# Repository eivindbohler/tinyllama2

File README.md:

<div id="summary" align="center">
  
</div>

<br/>

<br/>

- A fully-fledged 486/Pentium-class PC in a tiny form factor
- Integrated Sound Blaster Pro-compatible audio
- Add a Raspberry Pi Zero 2 for Roland MT&#8209;32 and General MIDI music
- Open-source hardware schematics, board layout and BIOS - build your own!
- Perfect for playing DOS games!

> **Note**  
> YouTube walkthrough + setup coming soon!

## Table of Contents
- [Summary](#summary)
- [Project Goals](#project-goals)
- [What's New In Version 2?](#whats-new-in-version-2)
- [Full system specs](#full-system-specs-revision-21)
- [Building](#building)
  * [Sourcing Parts](#sourcing-parts)
  * [Assembly](#assembly)
  * [Programming the CH559](#programming-the-ch559)
  * [Programming the BIOS](#programming-the-bios)
  * [Installing DOS](#installing-dos)
  * [Programming the CS4237B Firmware](#programming-the-cs4237b-firmware)
- [MT-32 / General MIDI](#mt-32--general-midi)
- [WiFi Connectivity](#wifi-connectivity)
- [Wiki](#wiki)
- [Help](#help)
- [Roadmap](#roadmap)
- [Contributing](#contributing)
- [License](#license)
- [Contact](#contact)
- [Acknowledgements](#acknowledgments)

<br/>

<div>

</div>

<br/>

## Project Goals
The goal of the TinyLlama project is:
- To create a fully x86-compatible DIY DOS computer with a sound card
- To keep the size as small as possible while keeping decent connectivity
- To keep the cost low

## What's New In Version 2?
Last year I released [version 1 of the TinyLlama][tinyllama1].  
While I was very happy with it and it worked great, there were a couple of things I felt were still missing + a few bugs.  

The two main new features in version 2 are:
* Built-in hardware USB HID (keyboard+mouse) to PS/2 emulation using [rasteri's HIDman firmware][hidman] running on a CH559 microcontroller  
* On-board Wemos D1 Mini ESP8266 for providing either a Hayes-compatible modem-over-WiFi or ethernet-over-WiFi (SLIP), depending on the firmware on the ESP.

Both the CH559 and the ESP8266 can be easily re-flashed/programmed in-place.  
Look at [Programming the CH559](#programming-the-ch559) and [Programming the ESP8266][wiki-wifi].

## Full system specs (revision 2.1)
### Hardware
- **86Duino System-on-module**
  * Vortex86EX CPU running at 60-500 MHz
  * 16 KB L1 cache (can be disabled)
  * 128 KB L2 cache
  * 128 MB DDR3 RAM
  * 8 MB programmable flash ROM
- **Vortex86VGA module running off a x1 PCI-e lane**
  * Maximum resolution: 1024x768, 60 Hz
  * 4 MB SRAM
  * [Alternative graphics cards][wiki-alternative-gpus]
- **Crystal CS4237B all-in-one audio chip**
- **12mm PC-speaker**
- **CR1220 battery for persistent real-time clock**
- **Power and reset buttons**
- **Connectivity**
  * USB-C for power
  * 2 x USB Type-A connectors for HID-compliant keyboard and mice
  * 2 x USB Type-A connectors for storage devices (USB 2.0)
  * MicroSD slot for storage
  * DE-9 RS232 serial port (COM1)
  * Modem or Ethernet/SLIP over WiFi (COM2)
  * Internal 2.54mm pin-header for connecting a fan (5V or 3.3V selectable)
  * 3.5mm line-out audio jack
- **mt32-pi subsystem**
  * 40-pin connector for a Raspberry Pi Zero 2
  * Pin headers for attaching a GY-PCM5102 I²S DAC module
  * Button for toggling between MT32 / General MIDI mode
  * Button for switching between audio ROMs / soundbanks
  * 4-pin I²C connector for an OLED display

### Software
- **[Custom Coreboot/SeaBIOS ROM][bios]**
- **MS-DOS / FreeDOS**

## Building
### Sourcing Parts
Full BOM (bill of materials) can be found [in the wiki][wiki-bom].
- The TinyLlama PCB rev2.1
- Modern SMD and through-hole components, as seen in the BOM
- 86Duino system-on-module (SOM-128-EX)
- Vortex86VGA Mini PCI-e module
- Crystal CS4237B 100-pin TQFP. Discontinued, but readily available
- Wemos D1 Mini ESP8266, optional
- A CR1220 battery if you want a persistent real-time clock
- One or more USB flash drives + an optional microSD card
- A USB-C power adapter (minimum 2A)

#### For MT-32/MIDI - optional
- GY-PCM5102 DAC module
- Raspberry Pi Zero 2 W with a microSD card
- An [mt32-pi compatible OLED display][mt32-pi-oled], optional but nice

### Assembly
Solder all components onto the TinyLlama rev2.1 PCB. As always, it's easier to start with the low-profile ones first, like resistors and capacitors.
If you're willing to spend slightly more, I recommended you let the PCB manufacturer pre-assemble most of the common components for you. Plus, some of the SMD components can be a bit tricky to solder.
Take a look at the [wiki][wiki-assembly] for more in-depth assembly instructions.

### Programming the CH559
1. Download the latest firmware binary from this repo, in the `hidman-binary` folder. Alternatively, get the latest source code from the [official repo][hidman] and compile it yourself.
2. Download and install `WCHISPTool_Setup.exe` from [WCH's website][wch]. Unfortunately, this tool only supports Windows. If you're on macOS or Linux, maybe try using virtualization software, or even another computer.
3. Open the `WCHISPTool_CH54x-55x` application.
4. Make sure the TinyLlama is powered off.
5. **Remove** the jumper from the "HID_POWER" pin header on the PCB (to ensure that the computer doesn't backpower the TinyLlama).
6. Connect a USB cable (type A to type A) between one of the HID USB ports on the TinyLlama and the Windows computer.
7. Press and hold the "PRG" button on the bottom side of the TinyLlama until the CH559 device pops up in the WCHISPTool.
8. Select the firmware binary file under _Download File -> Object File1_.
9. Click the "Download" button. Hopefully you'll get a success message in the log section on the right side of the program window.
10. Disconnect the USB cable.
11. **Add** the jumper to the "HID_POWER" pin header on the PCB.
12. Connect a keyboard to one of the HID USB ports. You should be good to go!

### Programming the BIOS
When purchasing the SOM-128-EX module from DMP, its ROM chip comes preinstalled with an Arduino-like bootloader which isn't what we want. Also, the  "crossbar" is configured for using the module with the 86Duino Zero/One boards - meaning its default pin layout is completely different from what we need for the TinyLlama.

Follow these steps to flash the ROM with the TinyLlama BIOS for the first time:
1. Find a USB flash drive, must be minimum 32 MB in size (shouldn't be a problem these days). Note that not all USB drives are bootable. Use a well-known bootable drive. _NB: You have to use a USB stick for this, an SD card won't work since the crossbar is configured to use different pins on the SOM for SD traffic._
2. Do a block-level transfer of the `INITBIOS.IMG` from this repo to the USB drive. Use [Balena Etcher][balena-etcher], or the command line if you know what you're doing (macOS example):
```
$ diskutil list
(Find your USB drive, eg. /dev/disk2)
$ diskutil unmountDisk /dev/disk2
$ sudo dd if=INITBIOS.IMG of=/dev/rdisk2 bs=1m
```
3. Insert the USB flash drive into the TinyLlama and turn it on. It'll hopefully boot into MS-DOS. Then, to flash the ROM:
```
C:\>anybios w initbios.rom
```
...and reboot.  

For subsequent BIOS updates, you can use the ROM's built-in virtual floppy drive available from the boot menu (press F12).  
When booted from this you'll only need a regular USB stick (formatted as FAT16/FAT32) containing the new BIOS file.

### Installing MS-DOS
_A note on selecting the DOS type:  
I've gone with MS-DOS 6.22 for maximum compatibility.  
If you prefer FreeDOS (or another DOS variant), prepare a bootable USB installer disk and use that instead of the built-in virtual floppy._
1. Pick a bootable USB drive or Micro SD card to use as the boot drive - for MS-DOS 6.22 you'll be limited to FAT16 and 2 GB per partition (though you can have several). For FreeDOS with FAT32 you can go all the way up to 2 TB.
2. Insert it, turn on the system, press F12 to bring up the boot menu, and select the virtual floppy drive.
3. Use `fdisk` from the command prompt to partition the SD/USB drive and set it to be `Active`.
4. Restart and again select to boot from the virtual floppy.  
Use `format c: /s /u` to format the drive and copy over system files. Finally use `fdisk /mbr` to make sure the Master Boot Record is correct and the drive should be bootable.
5. Copy over the `DOS` folder from A: to C:.  
You can either do this manually and create `CONFIG.SYS` and `AUTOEXEC.BAT` files to your liking, or more conveniently, just run the `SETUP.BAT` script that'll do this for you. The provided config files lets you choose from a clean boot or a QEMM-based one with XMS, EMS and 631 kB of free conventional memory.

### Programming the CS4237B Firmware
1. Copy the `CS4237B` and `UNISOUND` folders from this GitHub repo over to your SD/USB boot drive and start the system.
2. To program the firmware, run the `RESOURCE.EXE` command below and check that you get the same output:
```
C:\>cd cs4237b
C:\CS4237B>resource /f=0x120 /r=cs4237b.asm /e

Reading data from CS4237B.ASM
Length = 292    Programming EEPROM Block: 1 2    EEPROM programmed

Verifying EEPROM:
Verifying CS4237B.ASM against EEPROM . . .      Verified OKAY
```
3. Make sure the correct `BLASTER` environment variable is set and `UNISOUND.COM` command is called from `AUTOEXEC.BAT`. Note that the 8-bit DMA channel is **1** and the IRQ is **7**:
```
SET BLASTER=A220 I7 D1 P330 T4
C:\UNISOUND\UNISOUND.EXE /V60 /VW60 /VF60 /VL60 /VP60 /VC0 /VM0
```
4. Reboot the system, and you should get the following output:
```
Universal ISA PnP Sound Card Driver for DOS v0.76f. (c) JazeFox 2019-21
-----------------------------------------------------------------------
PnP card found: [CSC7537] CS4237B
BLASTER environment var found! Loading settings...
ADD:220 WSS:534 OPL:388 IRQ:7 DMA:1/1 MPU:330/I9 CTR:120 JOY:200
Initialization done.
Crystal Mixer [VOL:85 WAV:80 FM:80 LIN:0 CD:0 MIC:0]
```
5. Feel free to experiment with the different volume levels, look at the `C:\UNISOUND\UNISOUND.TXT` file for further guidance.
6. Fire up a few games to test that Adlib, SoundBlaster FM and digital sound effects are working properly.

## MT-32 / General MIDI
If you've installed [mt32-pi][mt32-pi] on a Raspberry Pi Zero 2 and connected it to the TinyLlama, it should be ready to go using IO port 330. Use the third button from the left (labeled "SYNTH_SW" on the PCB) to switch between MT-32 and General MIDI mode.  
If you want to play old games that require "MPU-401 Intelligent Mode" (Sierra games, Monkey Island 1, etc), try running [SoftMPU][softmpu]:
```
C:\SOFTMPU\>softmpu /mpu:330 /sb:220 /irq:7
```
If you want to hook up an I²C OLED display to the mt32-pi, there's a pin header on the TinyLlama labeled "I2C_OLED". The order of the pins from 1 to 4 is: GND, VCC, SCL, SDA with pin 1 being the one closest to the 3.5mm audio jack.

## WiFi Connectivity
There's a [section][wiki-wifi] in the wiki dedicated to this, take a look.

## Wiki
For an in-depth discussion of the various components, installation, configuration, etc, take a look at the [wiki][wiki].

## Help
This project is indended for people with a fair bit of hardware- and DOS knowledge. If you have questions or need help, please look at the [wiki][wiki] and [FAQ][wiki-faq] section first.

## Roadmap
Coming.  
In the mean time feel free to post [an issue][issues] if you have tips, suggestions or want to report an error.

## License
[GNU General Public License v3.0](LICENSE)

## Contact
Development thread: [Vogons][vogons-thread]  
Mastodon: [@eivindbohler@techhub.social][mastodon]  
Twitter: [@eivindbohler][twitter]  
YouTube: [@eivindbohler][youtube]

## Acknowledgements

Many thanks to
- [Sergey Kiselev][sergeys-projects] for sparking my interest in designing and building computers.
- [Rasteri][rasteri-videos] for introducing me to the CS4237B chip.
- [The Vogons forum][vogons] for inspiration, help and support.
- [86Duino / DMP][86duino] for making a great and affordable system-on-module.
- [Dale Whinham / mt32-pi][mt32-pi] for making the best synth emulator software.

[tinyllama1]: https://github.com/eivindbohler/tinyllama
[hidman]: https://github.com/rasteri/HIDman
[wiki-alternative-gpus]: https://github.com/eivindbohler/tinyllama2/wiki/alternative-gpus
[bios]: https://github.com/eivindbohler/tinyllama2-bios

[wiki]: https://github.com/eivindbohler/tinyllama2/wiki
[wiki-assembly]: https://github.com/eivindbohler/tinyllama2/wiki/assembly
[wiki-bom]: https://github.com/eivindbohler/tinyllama2/wiki/bom
[wiki-faq]: https://github.com/eivindbohler/tinyllama2/wiki/faq
[wiki-wifi]: https://github.com/eivindbohler/tinyllama2/wiki/wifi-connectivity

[balena-etcher]: https://www.balena.io/etcher
[mt32-pi-oled]: https://github.com/dwhinham/mt32-pi/wiki/LCD-and-OLED-display
[wch]: http://www.wch-ic.com/products/CH559.html

[issues]: https://github.com/eivindbohler/tinyllama2/issues

[vogons-thread]: https://www.vogons.org/viewtopic.php?t=84880
[mastodon]: https://techhub.social/@eivindbohler
[twitter]: https://twitter.com/eivindbohler
[youtube]: https://youtube.com/@eivindbohler

[sergeys-projects]: http://www.malinov.com/Home/sergeys-projects
[rasteri-videos]: https://www.youtube.com/user/TheRasteri/videos
[vogons]: https://www.vogons.org
[86duino]: https://www.86duino.com
[mt32-pi]: https://github.com/dwhinham/mt32-pi
[softmpu]: http://bjt42.github.io/softmpu

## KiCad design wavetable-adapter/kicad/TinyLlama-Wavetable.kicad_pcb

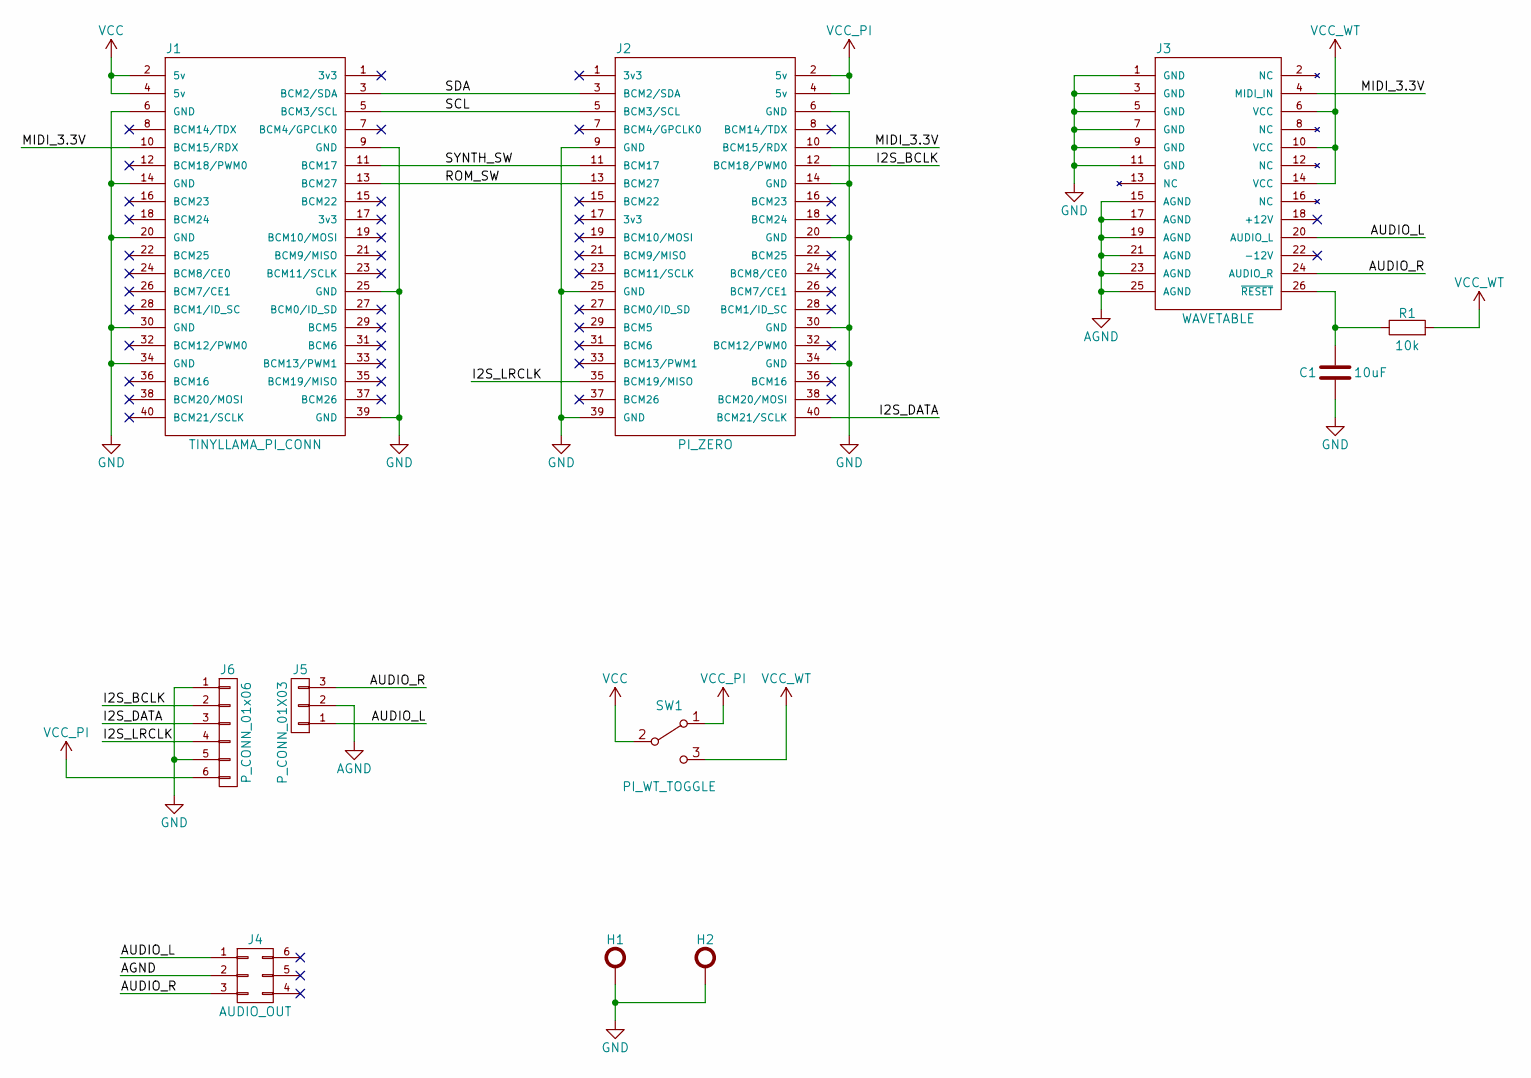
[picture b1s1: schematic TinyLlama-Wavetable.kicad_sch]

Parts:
C1: 10uF; C_0603_1608Metric
H1, H2: H_HOLE; H_440_HOLE
J1: TINYLLAMA_PI_CONN; J_CONN_RPI_MIRRORED_SMD
J2: PI_ZERO; J_CONN_RPI_SMD
J3: WAVETABLE; J_CONN_WAVETABLE
J4: AUDIO_OUT; P_CONN_02X03_SMD
J5: P_CONN_01X03; P_CONN_01X03_SMD
J6: P_CONN_01x06; P_CONN_01X06_SMD
R1: 10k; R_0603_1608Metric
SW1: PI_WT_TOGGLE; SW_1MS1T2B4M6QES

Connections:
/AUDIO_L: J3.20 (AUDIO_L), J4.1, J5.1
/AUDIO_R: J3.24 (AUDIO_R), J4.3, J5.3
/I2S_BCLK: J2.12 (BCM18/PWM0), J6.2
/I2S_DATA: J2.40 (BCM21/SCLK), J6.3
/I2S_LRCLK: J2.35 (BCM19/MISO), J6.4
/MIDI_3.3V: J1.10 (BCM15/RDX), J2.10 (BCM15/RDX), J3.4 (MIDI_IN)
/ROM_SW: J1.13 (BCM27), J2.13 (BCM27)
/SCL: J1.5 (BCM3/SCL), J2.5 (BCM3/SCL)
/SDA: J1.3 (BCM2/SDA), J2.3 (BCM2/SDA)
/SYNTH_SW: J1.11 (BCM17), J2.11 (BCM17)
AGND: J3.15 (AGND), J3.17 (AGND), J3.19 (AGND), J3.21 (AGND), J3.23 (AGND), J3.25 (AGND), J4.2, J5.2
GND: C1.2, H1.1, H2.1, J1.6 (GND), J1.9 (GND), J1.14 (GND), J1.20 (GND), J1.25 (GND), J1.30 (GND), J1.34 (GND), J1.39 (GND), J2.6 (GND), J2.9 (GND), J2.14 (GND), J2.20 (GND), J2.25 (GND), J2.30 (GND), J2.34 (GND), J2.39 (GND), J3.1 (GND), J3.3 (GND), J3.5 (GND), J3.7 (GND), J3.9 (GND), J3.11 (GND), J6.1, J6.5
unnamed: C1.1, J3.26 (~RESET), R1.1
VCC: J1.2 (5v), J1.4 (5v), SW1.2 (B)
VCC_PI: J2.2 (5v), J2.4 (5v), J6.6, SW1.1 (A)
VCC_WT: J3.6 (VCC), J3.10 (VCC), J3.14 (VCC), R1.2, SW1.3 (C)

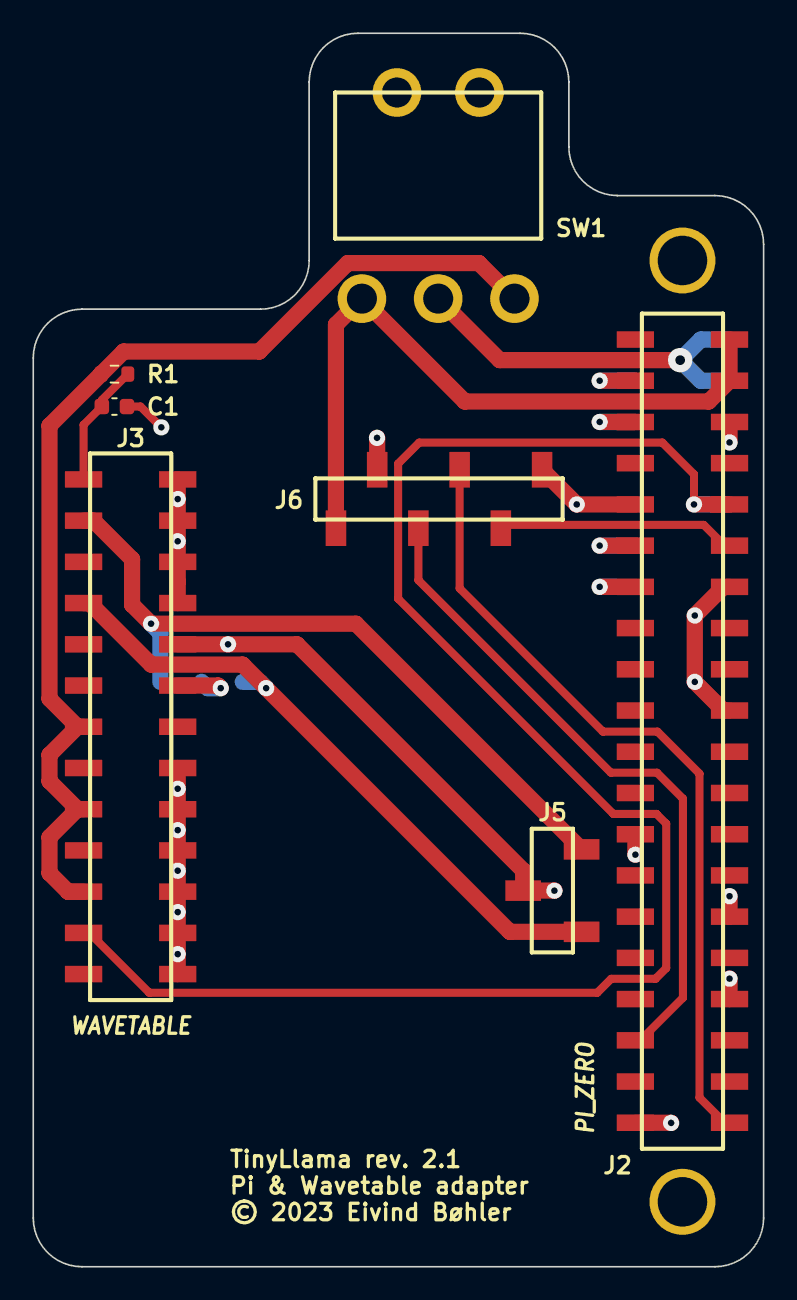
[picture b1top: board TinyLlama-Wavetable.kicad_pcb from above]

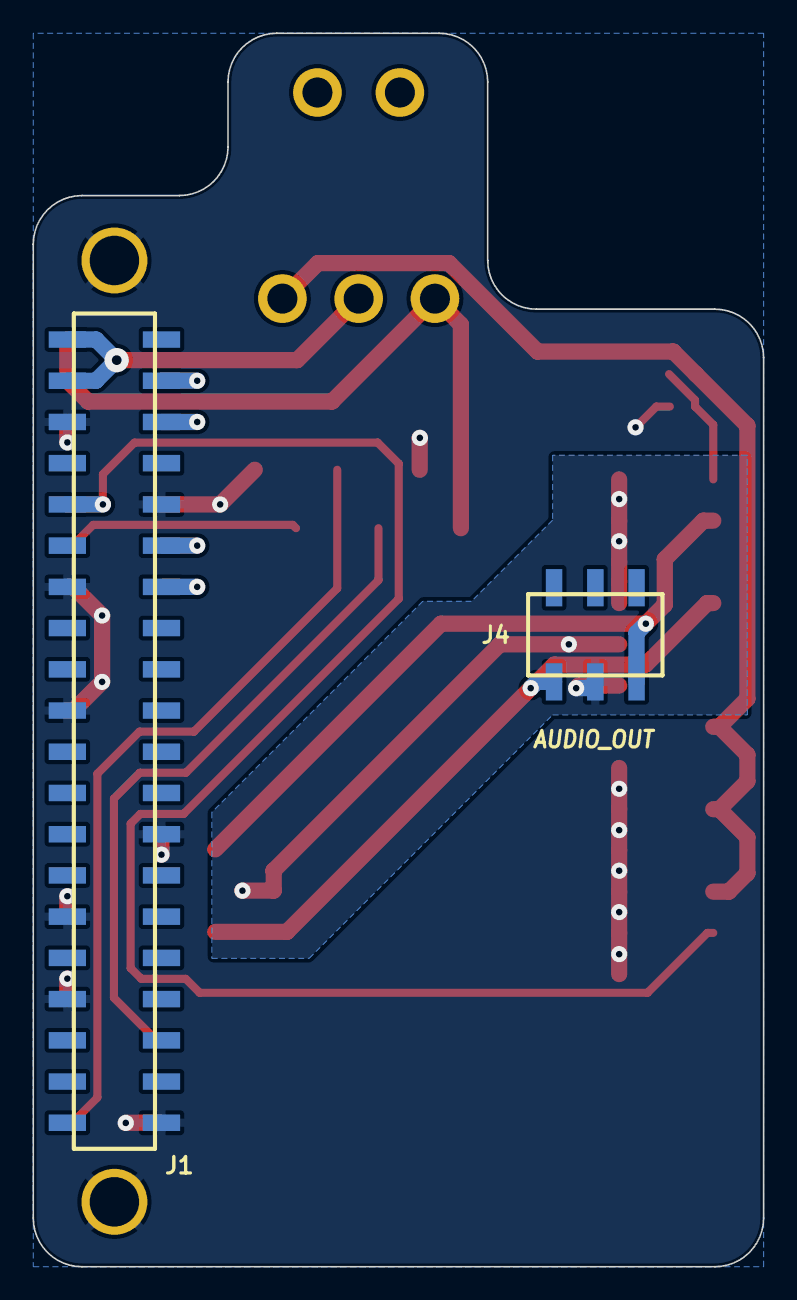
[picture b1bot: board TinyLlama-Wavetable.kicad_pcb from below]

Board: 2 copper layers, 45.0 x 76.0 mm, 11 parts (2 on the bottom side), 16 nets.

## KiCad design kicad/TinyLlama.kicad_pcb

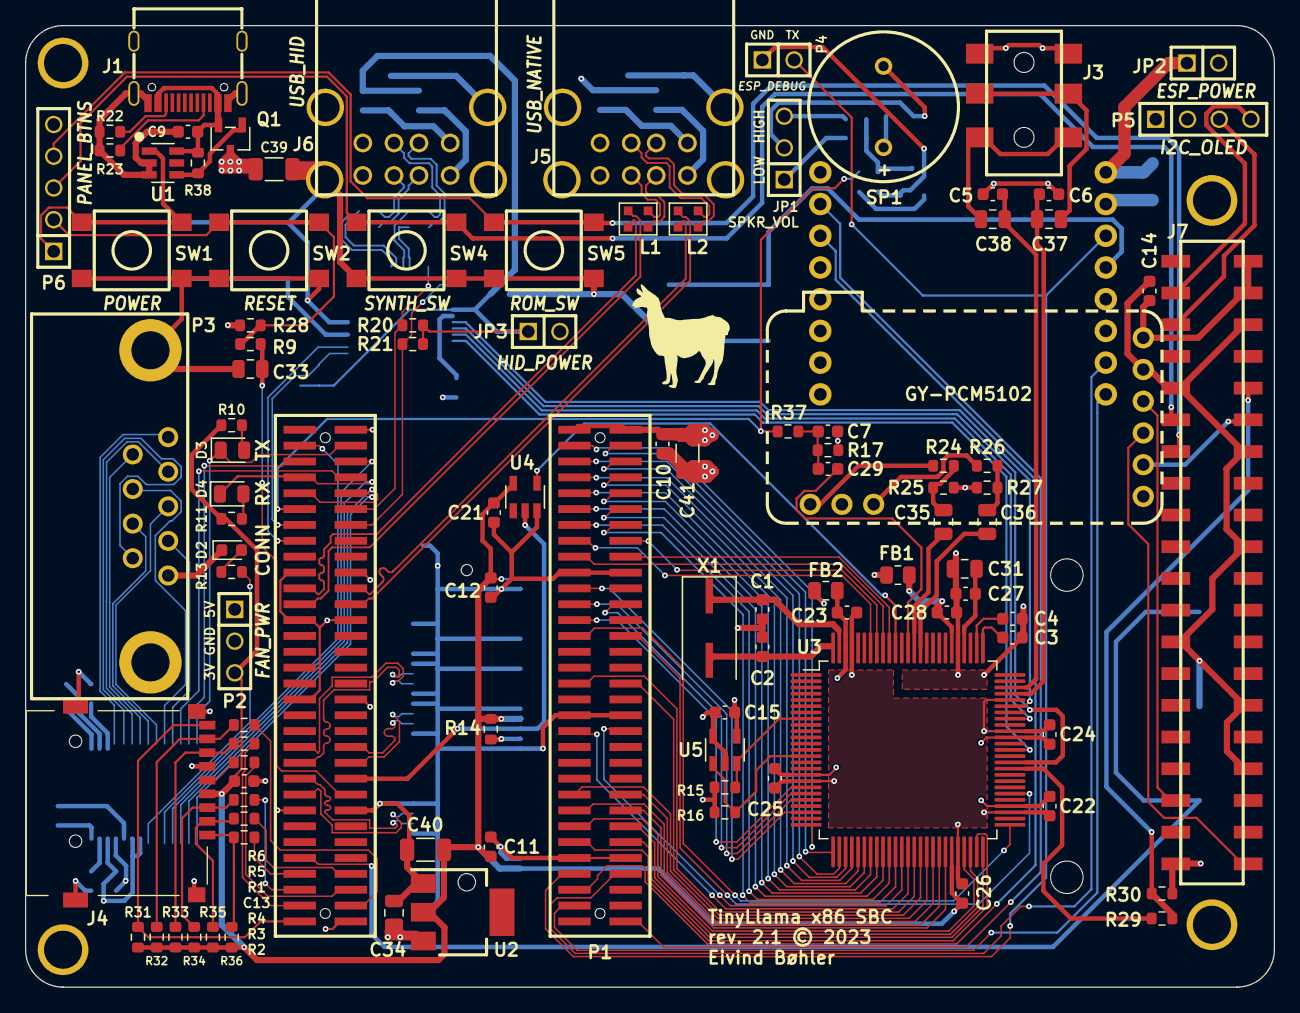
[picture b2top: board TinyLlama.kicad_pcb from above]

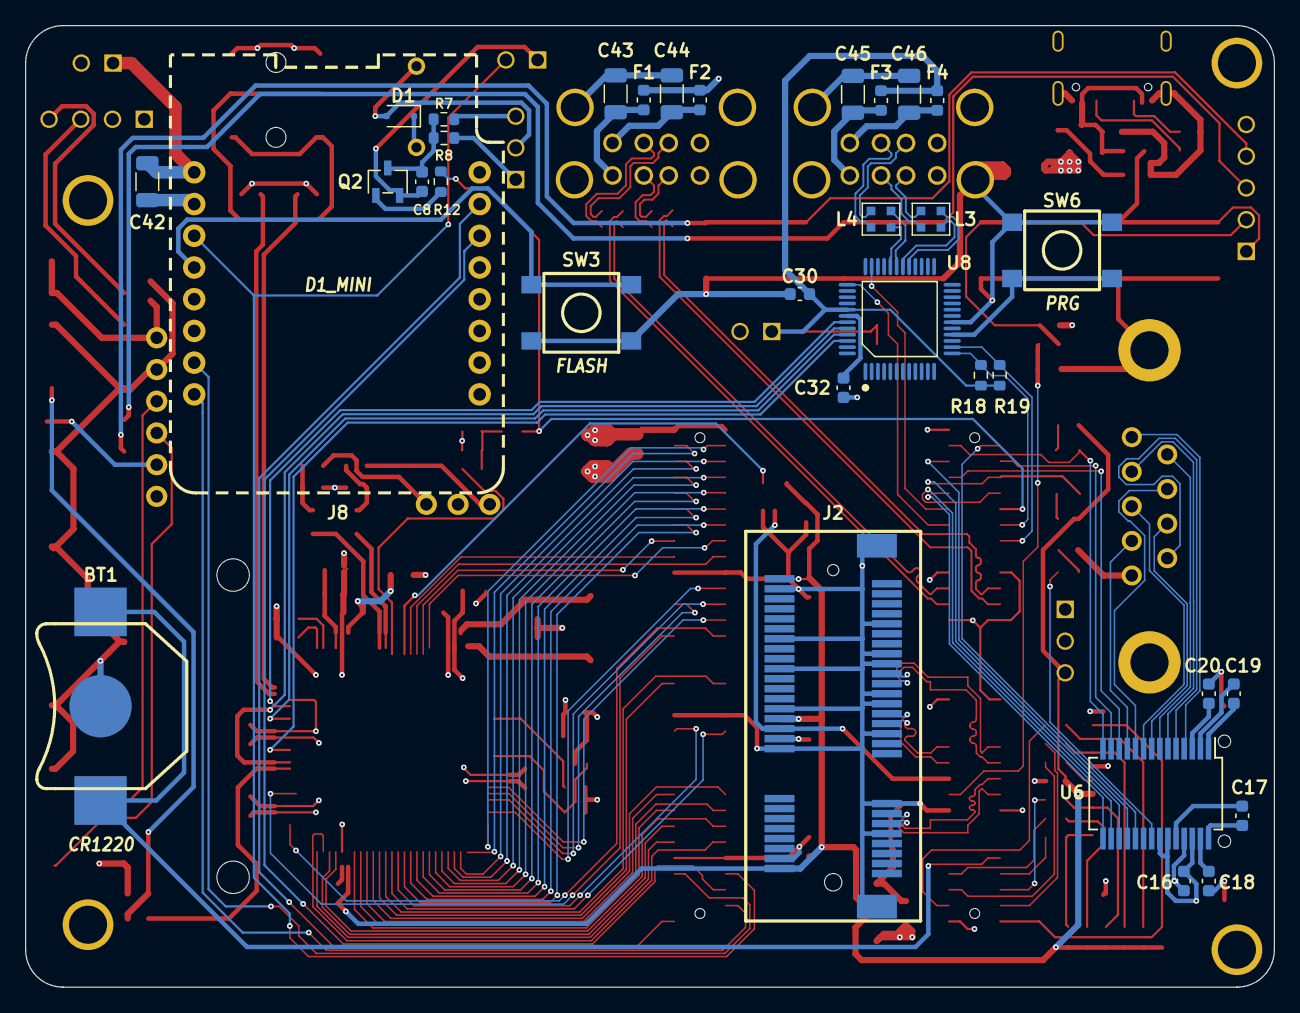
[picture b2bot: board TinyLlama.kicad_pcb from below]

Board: 4 copper layers, 100.0 x 77.0 mm, 139 parts (33 on the bottom side), 167 nets.

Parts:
BT1: CR1220; BT_MY-1220-03
C1, C2: 22pF; C_0603_1608Metric
C3, C4, C5, C6: 1nF; C_0603_1608Metric
C7: 2.7nF; C_0603_1608Metric
C8: 10nF; C_0603_1608Metric
C9, C10, C11, C12, C13, C14, C15, C16, C17, C18, C19, C20, C21, C22, C23, C24, C25, C26, C27, C28, C29, C30: 0.1uF; C_0603_1608Metric
C31: 1uF; C_0805_2012Metric
C32: 3.3uF; C_0603_1608Metric
C33, C34, C35, C36, C37, C38: 10uF; C_0805_2012Metric
C39, C40, C41, C42, C43, C44, C45, C46: 47uF; C_1206_3216Metric
D1: 1N4148; D_SOD-323F
D2: CONN; D_0603_1608Metric
D3: TX; D_0805_2012Metric
D4: RX; D_0805_2012Metric
F1, F2, F3, F4: F; Fuse_0603_1608Metric
FB1, FB2: FB; R_0805_2012Metric
H1, H2, H3, H4: H_HOLE; H_440_HOLE
J1: J_USB_C; J_USB_TYPE-C-31-M-12
J2: J_MINI_PCIE
J3: AudioJack3; J_AUDIO35_C95463
J4: MICRO_SD; J_MicroSD_TF01A
J5: USB_NATIVE; J_USB_A_C12049
J6: USB_HID; J_USB_A_C12049
J7: J_PI_ZERO; J_CONN_RPI_SMD
J8: D1_MINI; J_WEMOS_D1_MINI
JP1: SPKR_VOL; P_CONN_01X03_SQUARE
JP2: ESP_POWER; P_CONN_01X02_SQUARE
JP3: HID_POWER; P_CONN_01X02_SQUARE
L1, L2, L3, L4: L_EMI_FILTER; L_EMI_FILTER_MCM2012B900GBE
LOGO1: Llama_logo; LLAMA_LOGO
P1: P_SOM-128-EX; P_CONN_SOM-128-EX
P2: FAN_PWR; P_CONN_01X03_SQUARE
P3: P_DE9M
P4: ESP_DEBUG; P_CONN_01X02_SQUARE
P5: I2C_OLED; P_CONN_01X04_SQUARE
P6: PANEL_BTNS; P_CONN_01X05_SQUARE
Q1: Q_PMOS_GDS; Q_PFET_ENH_SOT-23-3
Q2: NPN; Q_BJT_SOT-23-3
R1: 0; R_0603_1608Metric
R2, R3, R4, R5, R6, R7: 33; R_0603_1608Metric
R8: 200; R_0603_1608Metric
R9: 470; R_0603_1608Metric
R10, R11, R12: 1k; R_0603_1608Metric
R13: 1.5k; R_0603_1608Metric
R14, R15, R16, R17, R18, R19, R20, R21: 4.7k; R_0603_1608Metric
R22, R23: 5.1k; R_0603_1608Metric
R24, R25, R26, R27: 6.8k; R_0603_1608Metric
R28, R29: 10k; R_0603_1608Metric
R30: 20k; R_0603_1608Metric
R31, R32, R33, R34, R35, R36, R37, R38: 47k; R_0603_1608Metric
SP1: SPEAKER; SP
SW1: POWER; SW_B3FS-1010
SW2: RESET; SW_B3FS-1010
SW3: FLASH; SW_B3FS-1010
SW4: SYNTH_SW; SW_B3FS-1010
SW5: ROM_SW; SW_B3FS-1010
SW6: PRG; SW_B3FS-1010
U1: U_MAX16054; U_TSOT-23-6
U2: U_AMS1117-3.3; U_SOT-223-3_NOTAB
U3: U_CS4237B-KQ; U_TQFP-100_14x14mm_P0.5mm_HandSoldering
U4: U_74LVC1G04; U_SOT-23-5
U5: U_K24C08; U_SOT-23-5
U6: U_MAX3243; U_SSOP-28_5.3x10.2mm_P0.65mm
U7: GY-PCM5102; U_GY-PCM5102
U8: U_CH559L; U_QFP-12x12_14x14_Pitch0.5mm
X1: 16.9344MHz; X_Crystal_SMD_HC49S-MINI

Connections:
+3.3V: C11.1, C12.1, C13.1, C21.1, C26.2, C40.1, J2.2 (+3V3AUX), J2.24 (+3V3AUX), J2.52 (+3V3AUX), J4.4 (VDD), P2.3 (+3.3V), R10.1, R11.1, R14.2, R31.1, R32.1, R33.1, R34.1, R35.1, R36.1, U2.2 (VOUT), U3.45 (VD1), U4.5 (VCC)
+5VA: C28.1, FB1.2, U3.81 (VA)
+5VFILT: C22.2, C23.2, C24.2, C25.2, FB2.2, U3.17 (VDF1), U3.54 (VDF4), U3.65 (VDF2), U3.98 (VDF3)
/3.3V_MIDI_OUT: J7.10 (BCM15/RDX), R29.2, R30.1
/A0: P1.B3 (GP70), U3.25 (SA0)
/A1: P1.B4 (GP71), U3.26 (SA1)
/A2: P1.B5 (GP72), U3.27 (SA2)
/A3: P1.B6 (GP73), U3.28 (SA3)
/A4: P1.B7 (GP74), U3.29 (SA4)
/A5: P1.B8 (GP75), U3.30 (SA5)
/A6: P1.B9 (GP76), U3.31 (SA6)
/A7: P1.B10 (GP77), U3.32 (SA7)
/A8: P1.B11 (GP60), U3.33 (SA8)
/A9: P1.B12 (GP61), U3.34 (SA9)
/A10: P1.B13 (GP62), U3.35 (SA10)
/A11: P1.B14 (GP63), U3.36 (SA11)
/A12: P1.B15 (GP64), U3.94 (SA12)
/A13: P1.B16 (GP65), U3.93 (SA13)
/A14: P1.B17 (GP66), U3.92 (SA14)
/A15: P1.B18 (GP67), U3.91 (SA15)
/AEN: P1.B33 (GP44), U3.39 (AEN)
/CS_SCL: R16.1, U3.14 (SCL/XA0), U5.1 (SCL)
/CS_SDA: R15.1, U3.8 (SDA/XD0), U5.3 (SDA)
/CTS1: P1.A10 (GP07), U6.15 (TTL_OUT5)
/CTS2: J8.7 (D8/GPIO15), P1.B64 (GP17)
/D0: P1.B47 (GP20), U3.41 (SD0)
/D1: P1.B48 (GP21), U3.42 (SD1)
/D2: P1.B49 (GP22), U3.43 (SD2)
/D3: P1.B50 (GP23), U3.44 (SD3)
/D4: P1.B51 (GP24), U3.47 (SD4)
/D5: P1.B52 (GP25), U3.48 (SD5)
/D6: P1.B53 (GP26), U3.49 (SD6)
/D7: P1.B54 (GP27), U3.50 (SD7)
/DCD1: P1.A3 (GP00), U6.19 (TTL_OUT1)
/DCD2: J8.11 (D4/GPIO2), P1.B57 (GP10), P4.2
/DRQ1: P1.B27 (GP56), U3.51 (DRQB(DRQ1*))
/DSR1: P1.A9 (GP06), U6.16 (TTL_OUT4)
/DTR1: P1.A8 (GP05), U6.12 (TTL_IN3)
/HID_VCC: C30.2, F3.1, F4.1, JP3.1, R18.2, R19.2, R20.2, R21.2, U8.41 (VIN5)
/I2S_BCLK: J7.12 (BCM18/PWM0), U7.2 (BCK)
/I2S_DATA: J7.40 (BCM21/SCLK), U7.3 (DIN)
/I2S_LRCLK: J7.35 (BCM19/MISO), U7.4 (LCK)
/IOCHRDY: P1.B34 (GP45), U3.40 (IOCHRDY)
/IRQ7: P1.B21 (GP50), U3.23 ((INT7*)IRQB)
/IRQ11: P1.B23 (GP52), U3.21 ((INT11*)IRQD)
/IRQ12: P1.B24 (GP53), U3.20 ((INT12*)IRQE)
/IRQ15: P1.B25 (GP54), U3.19 ((INT15*)IRQF)
/JAB1: U3.70 (JAB1), U8.43 (P1.0)
/JAB2: U3.61 (JAB2), U8.44 (P1.1)
/JACX: U3.68 (JACX), U8.45 (P1.2)
/JACY: U3.63 (JACY), U8.46 (P1.3)
/KBCLK: P1.A12 (GP91), R20.1, U8.35 (P0.5)
/KBDATA: P1.A14 (GP93), R21.1, U8.37 (P0.3)
/MIDI_AUDIO_L: R24.1, U7.7 (LOUT)
/MIDI_AUDIO_R: R26.1, U7.9 (ROUT)
/MIDI_OUT: R29.1, U3.60 (MIDOUT)
/MSCLK: P1.A13 (GP92), R18.1, U8.13 (P3.7)
/MSDATA: P1.A15 (GP94), R19.1, U8.14 (P4.3)
/PE0_CLK+: J2.13 (REFCLK+), P1.A47 (PE0_CLK+)
/PE0_CLK-: J2.11 (REFCLK-), P1.A45 (PE0_CLK-)
/PE0_RX+: J2.33 (PETp0), P1.A43 (PE0_RX+)
/PE0_RX-: J2.31 (PETn0), P1.A41 (PE0_RX-)
/PE0_TX+: J2.25 (PERp0), P1.A44 (PE0_TX+)
/PE0_TX-: J2.23 (PERn0), P1.A42 (PE0_TX-)
/PI_SCL: J7.5 (BCM3/SCL), P5.3 (SCL)
/PI_SDA: J7.3 (BCM2/SDA), P5.4 (SDA)
/PWR_SW: P6.1, SW1.2 (B), U1.1 (IN)
/RI1: P1.A6 (GP03), U6.18 (TTL_OUT2)
/ROM_SW: J7.13 (BCM27), P6.4, SW5.2 (B)
/RSTDRV: U3.90 (RESDRV), U4.4
/RST_SW: P6.2, R9.2, R28.2, SW2.2 (B)
/RS_CTS1: P3.8, U6.8 (RS_IN5)
/RS_DCD1: P3.1, U6.4 (RS_IN1)
/RS_DSR1: P3.6, U6.7 (RS_IN4)
/RS_DTR1: P3.4, U6.11 (RS_OUT3)
/RS_RI1: P3.9, U6.5 (RS_IN2)
/RS_RTS1: P3.7, U6.10 (RS_OUT2)
/RS_RX1: P3.2, U6.6 (RS_IN3)
/RS_TX1: P3.3, U6.9 (RS_OUT1)
/RTS1: P1.A5 (GP02), U6.13 (TTL_IN2)
/RTS2: J8.6 (D7/GPIO13), P1.B59 (GP12)
/RX1: D4.1 (K), P1.A7 (GP04), U6.17 (TTL_OUT3)
/RX2: J8.16 (TX/GPIO1), P1.B61 (GP14)
/SD_CD: J4.9 (CD), P1.A63 (GP86), R31.2
/SD_CLK: P1.A60 (GP83), R1.2
/SD_CMD: P1.A59 (GP82), R4.2
/SD_DAT0: P1.A61 (GP84), R5.2
/SD_DAT1: P1.A62 (GP85), R6.2
/SD_DAT2: P1.A57 (GP80), R2.2
/SD_DAT3: P1.A58 (GP81), R3.2
/SPKR: P1.A11 (GP90), R12.1, R37.1
/SYNTH_SW: J7.11 (BCM17), P6.3, SW4.2 (B)
/TX1: D3.1 (K), P1.A4 (GP01), U6.14 (TTL_IN1)
/TX2: J8.15 (RX/GPIO3), P1.B58 (GP11)
/USBD1+: L1.3, P1.A23 (USBD1+)
/USBD1-: L1.2, P1.A21 (USBD1-)
/USBD2+: L2.3, P1.A24 (USBD2+)
/USBD2-: L2.2, P1.A22 (USBD2-)
/USBDX1+: J5.3 (D1+), L1.4
/USBDX1-: J5.2 (D1-), L1.1
/USBDX2+: J5.7 (D2+), L2.4
/USBDX2-: J5.6 (D2-), L2.1
/USBHID1+: L3.4, U8.29 (P5.5/HP)
/USBHID1-: L3.1, U8.30 (P5.4/HM)
/USBHID2+: L4.4, U8.31 (P5.1/DP)
/USBHID2-: L4.1, U8.32 (P5.0/DM)
/USBHIDX1+: J6.3 (D1+), L3.3
/USBHIDX1-: J6.2 (D1-), L3.2
/USBHIDX2+: J6.7 (D2+), L4.3
/USBHIDX2-: J6.6 (D2-), L4.2
/VBATT: BT1.1 (+), P1.A55 (VBATT)
/VBUS: C9.2, J1.A4/B9 (VBUS), J1.A9/B4 (VBUS), Q1.3 (S), R38.2, U1.6 (VCC)
/X_SD_CLK: J4.5 (CLK), R1.1
/X_SD_CMD: J4.3 (CMD), R4.1, R34.2
/X_SD_DAT0: J4.7 (DAT0), R5.1, R33.2
/X_SD_DAT1: J4.8 (DAT1), R6.1, R32.2
/X_SD_DAT2: J4.1 (DAT2), R2.1, R36.2
/X_SD_DAT3: J4.2 (DAT3/CD), R3.1, R35.2
/~DACK1: P1.B28 (GP57), U3.56 (~DACKB(~DACK1*))
/~IOR: P1.B40 (GP31), U3.37 (~IOR)
/~IOW: P1.B39 (GP30), U3.38 (~IOW)
/~PCIRST: J2.22 (~PERST), P1.A46 (~PCIRST), U4.2
/~RST_SW: C33.1, P1.A48 (~RESET), R9.1
GND: BT1.2 (-), C1.1, C2.1, C3.2, C4.2, C5.2, C6.2, C7.2, C8.2, C9.1, C10.2, C11.2, C12.2, C13.2, C14.1, C15.2, C16.2, C18.2, C20.1, C21.2, C22.1, C23.1, C24.1, C25.1, C26.1, C27.2, C28.2, C30.1, C31.2, C32.1, C33.2, C34.2, C39.2, C40.2, C41.2, C42.2, C43.2, C44.2, C45.2, C46.2, D2.1 (K), H1.1, H2.1, H3.1, H4.1, J1.A1/B12 (GND), J1.A12/B1 (GND), J1.S (SHIELD), J2.4 (GND), J2.9 (GND), J2.15 (GND), J2.18 (GND), J2.21 (GND), J2.26 (GND), J2.27 (GND), J2.29 (GND), J2.34 (GND), J2.35 (GND), J2.37 (GND), J2.40 (GND), J2.43 (GND), J2.50 (GND), J2.S1 (SHIELD), J2.S2 (SHIELD), J3.S, J4.6 (VSS), J4.S (Shield), J5.4 (GND1), J5.8 (GND2), J5.S (Shield), J6.4 (GND1), J6.8 (GND2), J6.S (Shield), J7.6 (GND), J7.9 (GND), J7.14 (GND), J7.20 (GND), J7.25 (GND), J7.30 (GND), J7.34 (GND), J7.39 (GND), J8.10 (GND), P1.A2 (GND), P1.A19 (GND), P1.A20 (GND), P1.A25 (AGND), P1.A26 (AGND), P1.A35 (GND), P1.A36 (GND), P1.A49 (GND), P1.A50 (GND), P1.A64 (GP87), P1.B19 (GND), P1.B20 (GND), P1.B37 (GND), P1.B38 (GND), P1.B55 (GND), P1.B56 (GND), P2.2 (GND), P3.5, P3.10 (GND), P3.11 (GND), P4.1, P5.1 (GND), P6.5, Q2.2 (E), R17.2, R22.2, R23.2, R25.2, R27.2, R30.2, SW1.1 (A), SW2.1 (A), SW3.2 (B), SW4.1 (A), SW5.1 (A), SW6.2 (B), U1.2 (GND), U1.3 (CLEAR), U2.1 (GND), U3.18 (SGND1), U3.46 (DGND1), U3.53 (SGND4), U3.66 (SGND2), U3.71 (TEST), U3.80 (AGND), U3.97 (SGND3), U4.3 (GND), U5.2 (GND), U5.5 (WP), U6.25 (GND), U7.1 (SCK), U7.5 (GND), U7.8 (AGND), U8.18 (GND)
unnamed: C7.1, C29.2, R17.1, R37.2
unnamed: C35.2, R24.2, R25.1
unnamed: C36.2, R26.2, R27.1
unnamed: C37.2, J3.R
unnamed: C38.2, J3.T
unnamed: D1.2 (A), JP1.2, SP1.2
unnamed: D2.2 (A), R13.2
unnamed: D3.2 (A), R10.2
unnamed: D4.2 (A), R11.2
unnamed: J1.A5 (CC1), R23.1
unnamed: J1.B5 (CC2), R22.1
unnamed: J2.20 (~W_DISABLE), R14.1
unnamed: C43.1, F1.2, J5.1 (VBUS1)
unnamed: C44.1, F2.2, J5.5 (VBUS2)
unnamed: C45.1, F3.2, J6.1 (VBUS1)
unnamed: C46.1, F4.2, J6.5 (VBUS2)
unnamed: C42.1, J8.9 (5V), JP2.1
unnamed: J8.12 (D3/GPIO0), SW3.1 (A)
unnamed: JP1.1, R8.2
unnamed: JP1.3, R7.2
unnamed: Q1.1 (G), R38.1, U1.4 (~OUT)
unnamed: Q2.1 (B), R12.2
unnamed: C8.1, Q2.3 (C), R7.1, R8.1
unnamed: SW6.1 (A), U8.16 (P4.6)
unnamed: C4.1, U3.77 (LFILT)
unnamed: C35.1, U3.87 (LLINE)
unnamed: C5.1, C38.1, U3.73 (LOUT)
unnamed: C29.1, U3.88 (MIN)
unnamed: C27.1, C31.1, U3.79 (REFFLT)
unnamed: C3.1, U3.76 (RFILT)
unnamed: C36.1, U3.86 (RLINE)
unnamed: C6.1, C37.1, U3.72 (ROUT)
unnamed: C2.2, U3.100 (XTALI), X1.2
unnamed: C1.2, U3.99 (XTALO), X1.1
unnamed: C17.1, U6.28 (C1+)
unnamed: C17.2, U6.24 (C1-)
unnamed: C19.1, U6.1 (C2+)
unnamed: C19.2, U6.2 (C2-)
unnamed: C18.1, U6.27 (V+)
unnamed: C20.2, U6.3 (V-)
unnamed: R13.1, U6.21 (~INVALID)
unnamed: C32.2, U8.42 (VDD33)
VCC: C10.1, C14.2, C15.1, C16.1, C34.1, C39.1, C41.1, D1.1 (K), F1.1, F2.1, FB1.1, FB2.1, J7.2 (5v), J7.4 (5v), JP2.2, JP3.2, P1.B1 (VCC), P1.B2 (VCC), P2.1 (+5V), P5.2 (VCC), Q1.2 (D), R15.2, R16.2, R28.1, SP1.1, U2.3 (VIN), U5.4 (VCC), U6.22 (~FORCEOFF), U6.23 (FORCEON), U6.26 (VCC), U7.6 (VIN)

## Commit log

2023-02-17 Make git ignore Kicad cache files
2023-02-17 Add section about MT-32/GM
2023-02-26 Added files required to enable USB CD drive on TinyLlama2 board
2023-03-07 Update INITBIOS, README
2023-03-09 Add I2C_OLED pinout to README
2023-03-18 Update INITBIOS
2023-04-25 Add example case 3d models
2023-08-18 add wavetable adapter kicad files
2023-08-21 Add files via upload
    updated schematic to add +/-12 DC2DC and 3v3 to 5v level shifter.
    PCB and footprint for PDME2-S5-D12 is still remaining

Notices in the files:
kicad/TinyLlama.kicad_pcb:
rev. 2.1 © 2023
wavetable-adapter/kicad/TinyLlama-Wavetable.kicad_pcb:
© 2023 Eivind Bøhler
